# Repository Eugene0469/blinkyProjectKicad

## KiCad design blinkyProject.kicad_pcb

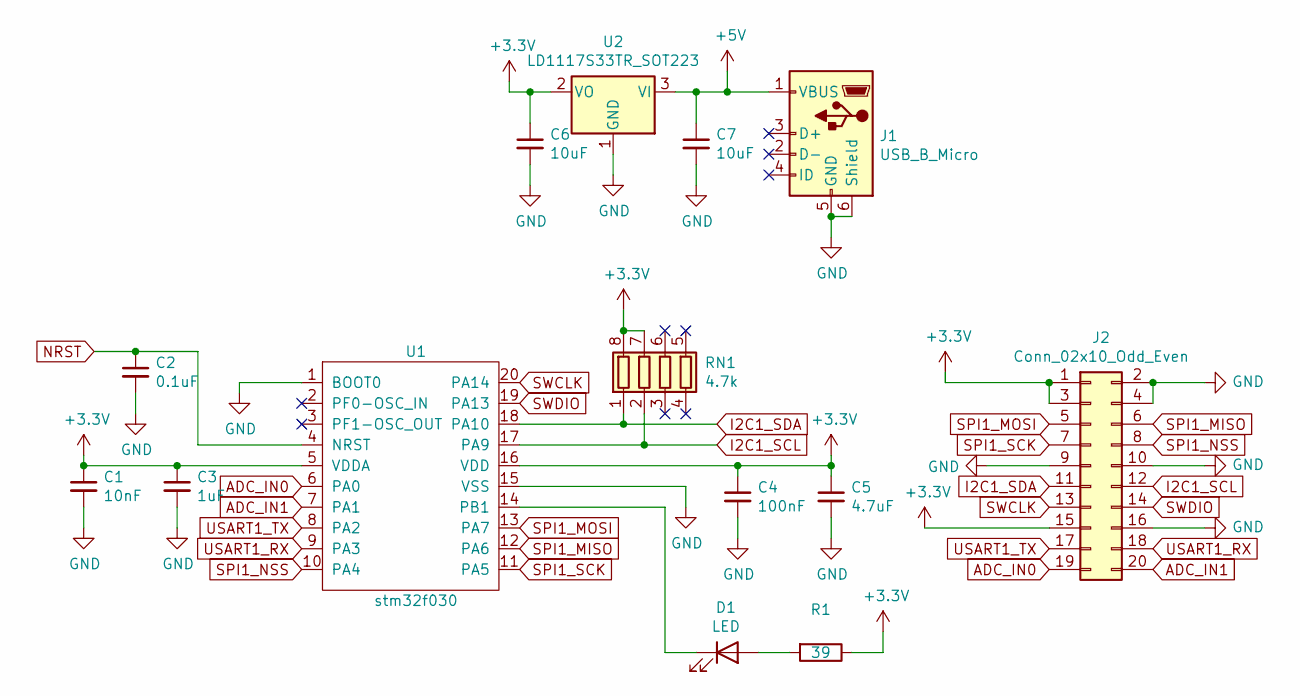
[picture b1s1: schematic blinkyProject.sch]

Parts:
C1: 10nF; C_0805_2012Metric_Pad1.18x1.45mm_HandSolder
C2: 0.1uF; C_0805_2012Metric_Pad1.18x1.45mm_HandSolder
C3: 1uF; C_0805_2012Metric_Pad1.18x1.45mm_HandSolder
C4: 100nF; C_0805_2012Metric_Pad1.18x1.45mm_HandSolder
C5: 4.7uF; C_0805_2012Metric_Pad1.18x1.45mm_HandSolder
C6, C7: 10uF; C_0805_2012Metric_Pad1.18x1.45mm_HandSolder
D1: LED; LED_0805_2012Metric_Pad1.15x1.40mm_HandSolder
J1: USB_B_Micro; USB_Micro-B_Molex-105017-0001
J2: Conn_02x10_Odd_Even; PinHeader_2x10_P2.54mm_Vertical
R1: 39; R_0805_2012Metric_Pad1.20x1.40mm_HandSolder
RN1: 4.7k; R_Array_Convex_4x0603
U1: stm32f030; TSSOP-20_4.4x6.5mm_P0.65mm
U2: LD1117S33TR_SOT223; SOT-223-3_TabPin2

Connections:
+3V3: C1.1, C3.1, C4.1, C5.1, C6.1, J2.1, J2.3, J2.15, R1.1, RN1.7 (R2.2), RN1.8 (R1.2), U1.5 (VDDA), U1.16 (VDD), U2.2 (VO)
+5V: C7.1, J1.1 (VBUS), U2.3 (VI)
ADC_IN0: J2.19, U1.6 (PA0)
ADC_IN1: J2.20, U1.7 (PA1)
GND: C1.2, C2.2, C3.2, C4.2, C5.2, C6.2, C7.2, J1.5 (GND), J1.6 (Shield), J2.2, J2.4, J2.9, J2.10, J2.16, U1.1 (BOOT0), U1.15 (VSS), U2.1 (GND)
I2C1_SCL: J2.12, RN1.2 (R2.1), U1.17 (PA9)
I2C1_SDA: J2.11, RN1.1 (R1.1), U1.18 (PA10)
NRST: C2.1, U1.4 (NRST)
unnamed: D1.1 (K), U1.14 (PB1)
unnamed: D1.2 (A), R1.2
SPI1_MISO: J2.6, U1.12 (PA6)
SPI1_MOSI: J2.5, U1.13 (PA7)
SPI1_NSS: J2.8, U1.10 (PA4)
SPI1_SCK: J2.7, U1.11 (PA5)
SWCLK: J2.13, U1.20 (PA14)
SWDIO: J2.14, U1.19 (PA13)
USART1_RX: J2.18, U1.9 (PA3)
USART1_TX: J2.17, U1.8 (PA2)

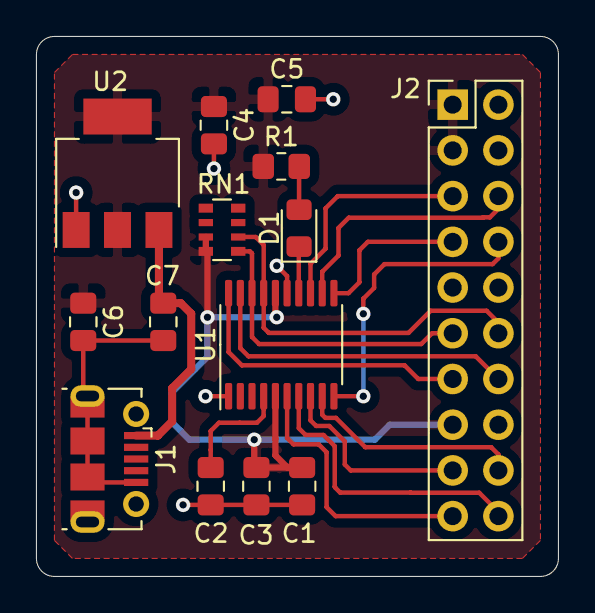
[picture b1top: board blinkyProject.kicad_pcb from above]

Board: 2 copper layers, 29.0 x 30.0 mm, 14 parts (0 on the bottom side), 18 nets.

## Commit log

2021-07-24 Completes schematic design
2021-07-24 Annotates schematic
2021-07-24 Adds .gitignore file'
2021-07-24 Generates Netlist
2021-07-24 Assigns footprints to schematic symbol
2021-07-24 Adds capacitor C6 and C7
2021-07-24 Placed power and gnd planes
2021-07-25 Adds custom lib
2021-07-25 Rearranges pin connections
2021-07-25 Completes routing
2021-07-25 Adds schematic pdf plot
2021-07-25 Ignores gerber and drill files
2021-07-25 Adds gerber job file'
2021-07-25 Closes the pcb brd file
